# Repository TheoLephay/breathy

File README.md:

# Breathy

Work in progress.

An IOT esp32-based, battery powered, air quality monitor.

Since this is the least original project but I still needed one, I decided to make the li-ion charger myself as a challenge with discreet components.

Hardware design sheets available under `hardware/breathy/` folder. SPICE sim under `hardware/spice_sims/`.

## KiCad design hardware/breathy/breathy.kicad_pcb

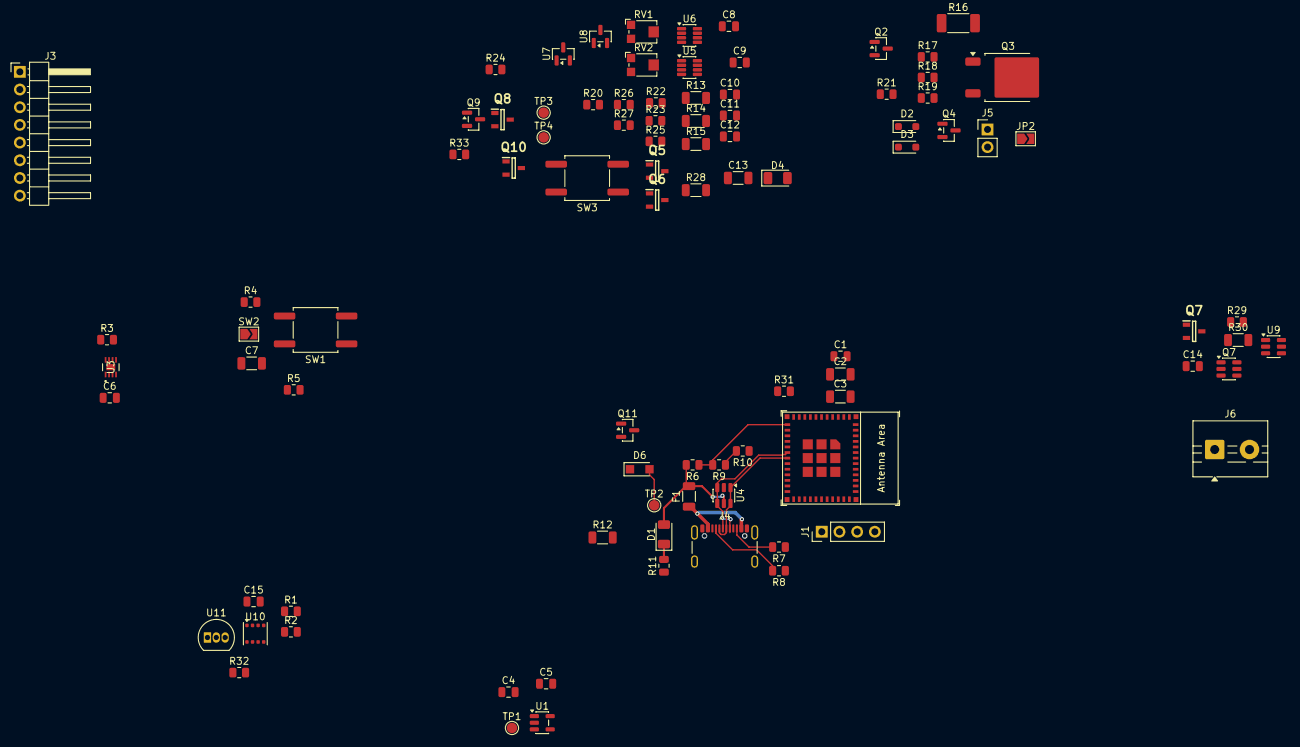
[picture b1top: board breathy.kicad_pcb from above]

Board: 4 copper layers, 91 parts (0 on the bottom side), 62 nets.

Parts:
C1, C5, C6, C8, C9, C14, C15: 0.1u; C_0805_2012Metric
C2, C3: 10u; C_1206_3216Metric
C4: 10u; C_0805_2012Metric
C7, C13: 1u; C_1206_3216Metric
C10, C11, C12: 1nF; C_0805_2012Metric
D1: LED R; LED_1206_3216Metric
D2, D3: D_Schottky; D_SOD-323_HandSoldering
D4: LED G; LED_1206_3216Metric
D6: RB168MM-40TR; Nexperia_CFP3_SOD-123W
F1: Polyfuse; C_1206_3216Metric
J1: Conn_01x04_Pin; PinHeader_1x04_P2.54mm_Vertical
J3: EPD; PinHeader_1x08_P2.54mm_Horizontal
J4: USB_C_Receptacle_USB2.0_16P; USB_C_Receptacle_GCT_USB4105-xx-A_16P_TopMnt_Horizontal
J5: Conn_01x02_Pin; PinHeader_1x02_P2.54mm_Vertical
J6: Screw_Terminal_01x02; TerminalBlock_MaiXu_MX126-5.0-02P_1x02_P5.00mm
JP2: Jumper_2_Small_Open; SolderJumper-2_P1.3mm_Open_TrianglePad1.0x1.5mm
Q2, Q4: MMBT3906; SOT-23
Q3: 2SAR572D3TL1; TO-252-2
Q5, Q6, Q7#2, Q8, Q10: PMV37ENEAR; SOT95P230X110-3N
Q7: FS8205A; SOT-23-6
Q9, Q11: DMG3415U-7; SOT-23
R1, R2, R7, R8, R10, R19, R32: 5.1k; R_0805_2012Metric
R3, R4, R5, R6, R9, R17, R18, R20, R21, R25, R27, R31: 10k; R_0805_2012Metric
R11, R22, R24: 150; R_0805_2012Metric
R12, R13, R14, R28: 100k; R_1206_3216Metric
R15: 1k; R_1206_3216Metric
R16: 0R100; R_2010_5025Metric_Pad1.40x2.65mm_HandSolder
R23: 0R; R_0805_2012Metric
R26: 6k8; R_0805_2012Metric
R29: 470R; R_0805_2012Metric
R30: 1K; R_1206_3216Metric
R33: 1M; R_0805_2012Metric
RV1, RV2: 20K; Potentiometer_Bourns_TC33X_Vertical
SW1: SW_Push; SW_Push_1P1T_NO_CK_KSC9xxG
SW2: SW_Push; SolderJumper-2_P1.3mm_Open_TrianglePad1.0x1.5mm
SW3: CHG RST; SW_Push_1P1T_NO_CK_KSC9xxG
TP1, TP2, TP3, TP4: TestPoint; TestPoint_Pad_D1.5mm
U1: TLV75533PDBVR; SOT-23-5
U2: ESP32-C6-MINI-1/U; ESP32-C6-MINI-1
U3: MAX17048G+; 21-0168_T822&plus_3_MXM-M
U4: USBLC6-2SC6; SOT-23-6
U5, U6: TLV9002; TSOT-23-8
U7, U8: AZ431AN; SOT-23
U9: DW01A; SOT-23-6
U10: BME690; Bosch_LGA-8_3x3mm_P0.8mm_ClockwisePinNumbering
U11: DS18B20; TO-92_Inline

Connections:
+3V3: C1.1, C2.1, C3.1, C5.1, C15.2, J3.8, R1.2, R3.2, R4.2, R5.2, TP1.1 (1_1), U1.5 (OUT), U2.3 (3V3), U10.2 (CSB), U10.6 (VDDIO), U10.8 (VDD), U11.3 (V_{DD})
+BATT: C6.1, J6.2, Q9.2 (S), Q11.3 (D), R29.1, R33.2, U3.2 (CELL), U3.3 (VDD)
/1w: R32.1, U2.19 (GPIO14), U11.2 (DQ)
/BUSY: J3.1, U2.28 (GPIO22)
/CS: J3.4, U2.25 (GPIO19)
/Charger/V_shunt: Q3.3 (E), R16.2, R19.1, R20.2, U6.6 (-)
/Charger/chrg_out: J5.1, JP2.1 (A), Q9.3 (D), R23.1
/Charger/i_end: RV1.2, TP3.1 (1_1), U6.5 (+)
/Charger/i_max: RV2.2, TP4.1 (1_1), U5.3 (+), U5.5 (+)
/D+: J4.A6 (D+), J4.B6 (D+), U2.18 (GPIO13/USB_D+), U4.1 (I/O1), U4.6 (I/O1)
/D-: J4.A7 (D-), J4.B7 (D-), U2.17 (GPIO12/USB_D-), U4.3 (I/O2), U4.4 (I/O2)
/D/C: J3.3, U2.26 (GPIO20)
/RES: J3.2, U2.27 (GPIO21)
/SCL: J3.5, U2.24 (GPIO18)
/SDA: J3.6, U2.20 (GPIO15)
/batt_alrt: R3.1, U2.5 (GPIO2/ADC1_CH2), U3.5 (*ALRT)
/chip_en: C7.1, R5.1, SW1.2, U2.8 (EN/CHIP_PU)
/chrg_end_ind_n: Q5.1, Q6.3, Q8.3, Q10.1, R17.1, R18.1, R31.2
/chrg_end_req: Q8.1, U2.29 (GPIO23)
/gpio8_pu: R4.1, U2.22 (GPIO8)
/gpio9_dl: SW2.2, U2.23 (GPIO9)
/i2c_scl: R1.1, U2.16 (MTDO/GPIO7), U3.7 (SCL), U10.4 (SCK)
/i2c_sda: R2.1, U2.15 (MTCK/GPIO6/ADC1_CH6), U3.8 (SDA), U10.3 (SDI)
/usb_conn: R6.1, R9.2, U2.12 (GPIO0/ADC1_CH0/XTAL_32K_P)
GND: C1.2, C2.2, C3.2, C4.2, C5.2, C6.2, C7.2, C8.2, C9.2, C11.1, C13.2, C15.1, J1.4, J3.7, J4.A1 (GND), J4.A12 (GND), J4.B1 (GND), J4.B12 (GND), J4.SH (SHIELD), Q4.3 (C), Q5.2, Q7.3 (S2), Q8.2, Q10.2, R7.1, R8.1, R10.1, R11.1, R12.2, R15.2, R21.2, R27.1, R30.2, SW1.1, SW2.1, SW3.1, U1.2 (GND), U2.1 (GND), U2.2 (GND), U2.11 (GND), U2.14 (GND), U2.36 (GND), U2.37 (GND), U2.38 (GND), U2.39 (GND), U2.40 (GND), U2.41 (GND), U2.42 (GND), U2.43 (GND), U2.44 (GND), U2.45 (GND), U2.46 (GND), U2.47 (GND), U2.48 (GND), U2.49 (GND), U2.50 (GND), U2.51 (GND), U2.52 (GND), U2.53 (GND), U3.1 (CTG), U3.4 (GND), U3.6 (QSTRT), U3.9 (EPAD), U4.2 (GND), U5.4 (V-), U6.4 (V-), U8.3 (A), U10.1 (GND), U10.5 (SDO), U10.7 (GND), U11.1 (GND)
unnamed: C13.1, Q6.1, R28.2, SW3.2
unnamed: D1.1 (K), R11.2
unnamed: C10.2, D2.2 (A), U5.7
unnamed: D2.1 (K), D3.1 (K), Q2.3 (C), Q4.1 (B), R21.1
unnamed: C12.2, D3.2 (A), U6.1
unnamed: D4.1 (K), R22.2
unnamed: C4.1, D6.1 (K), Q11.2 (S), U1.1 (IN), U1.3 (EN)
unnamed: F1.1, J4.A4 (VBUS), J4.A9 (VBUS), J4.B4 (VBUS), J4.B9 (VBUS)
unnamed: J1.2, U2.30 (U0RXD/GPIO17)
unnamed: J1.3, U2.31 (U0TXD/GPIO16)
unnamed: J4.A5 (CC1), R8.2
unnamed: J4.B5 (CC2), R7.2
unnamed: J5.2, JP2.2 (B), Q3.2 (C)
unnamed: C14.2, J6.1, Q7.1 (S1), Q7#2.2, U9.6 (GND)
unnamed: Q2.1 (B), R18.2
unnamed: Q3.1 (B), Q4.2 (E), R19.2
unnamed: Q5.3, R22.1
unnamed: Q6.2, U6.7
unnamed: Q7.2 (D1), Q7.5 (D2)
unnamed: Q7.6 (G1), U9.1 (OD)
unnamed: Q7.4 (G2), U9.3 (OC)
unnamed: Q9.1 (G), Q10.3, R33.1
unnamed: R2.2, R32.2
unnamed: R9.1, R10.2
unnamed: R13.1, RV1.3
unnamed: R14.1, RV2.3
unnamed: R31.1, U2.13 (GPIO1/ADC1_CH1/XTAL_32K_N)
unnamed: R13.2, U5.1, U5.2 (-)
unnamed: C10.1, R20.1, U5.6 (-)
unnamed: C11.2, R23.2, U6.3 (+)
unnamed: C12.1, R25.2, U6.2 (-)
unnamed: R14.2, R15.1, U7.3 (A)
unnamed: R24.1, R25.1, R26.2, U8.2 (K)
unnamed: R26.1, R27.2, U8.1 (REF)
unnamed: R30.1, U9.2 (CS)
unnamed: C14.1, R29.2, U9.5 (VCC)
VBUS: C8.1, C9.1, D1.2 (A), D4.2 (A), D6.2 (A), F1.2, Q2.2 (E), Q11.1 (G), R6.2, R12.1, R16.1, R17.2, R24.2, R28.1, RV1.1, RV2.1, TP2.1 (1_1), U4.5 (VBUS), U5.8 (V+), U6.8 (V+), U7.1 (REF), U7.2 (K)
